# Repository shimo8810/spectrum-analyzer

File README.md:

# Spectrum Analyzer

This is a stereo 7-band spectrum analyzer utilizing the MSGEQ7.

## Tools

### LED Matrix Generator

this tool is for generating data for LED matrix.

[LED Matrix Generator Web App](https://shimo8810.github.io/spectrum-analyzer/)

## License

- Software: [MIT License](https://choosealicense.com/licenses/mit/)
- Hardware: [CERN Open Hardware License version 2.0](https://choosealicense.com/licenses/cern-ohl-p-2.0/)

## Acknowledgments

- [Equalizer icons created by Ehtisham Abid - Flaticon](https://www.flaticon.com/free-icons/equalizer)

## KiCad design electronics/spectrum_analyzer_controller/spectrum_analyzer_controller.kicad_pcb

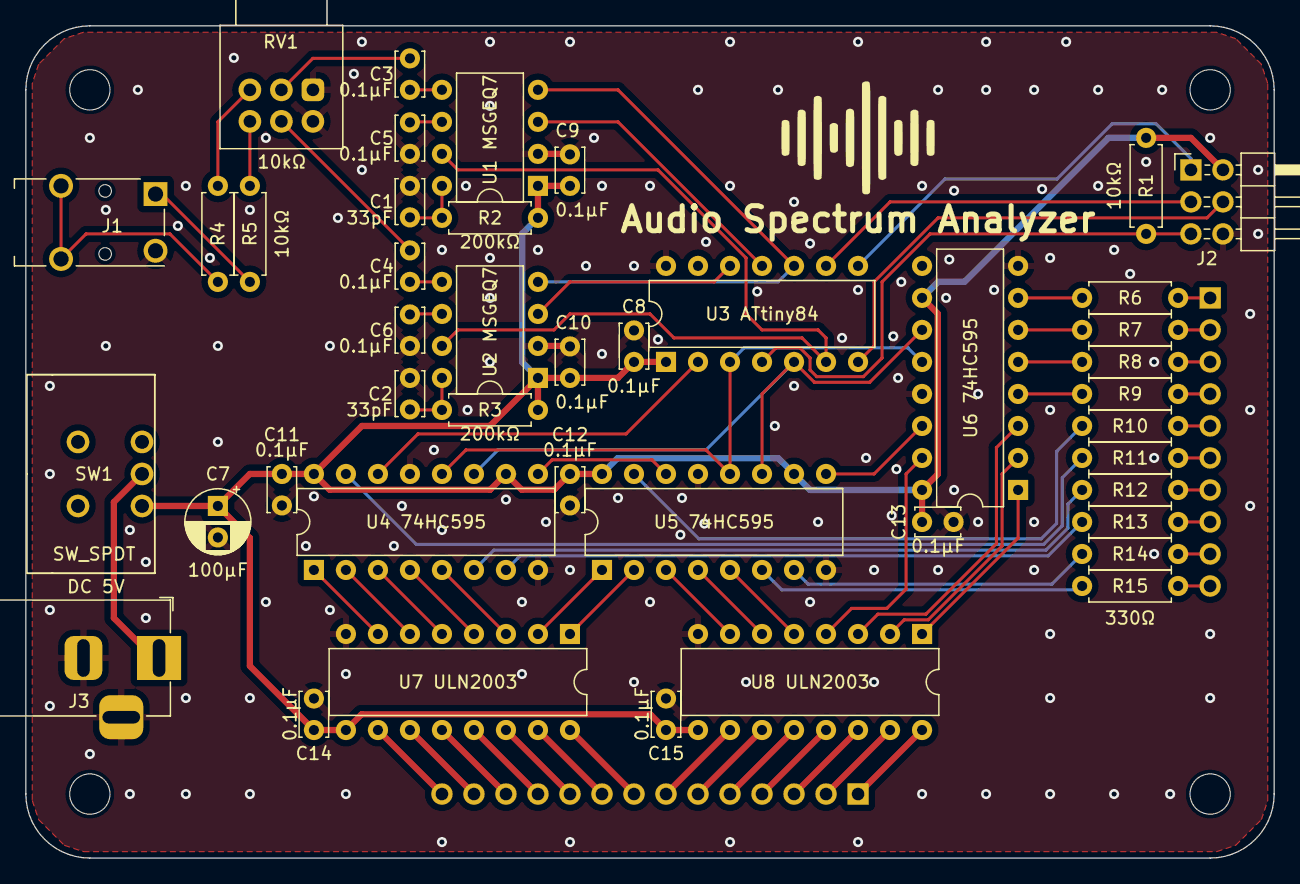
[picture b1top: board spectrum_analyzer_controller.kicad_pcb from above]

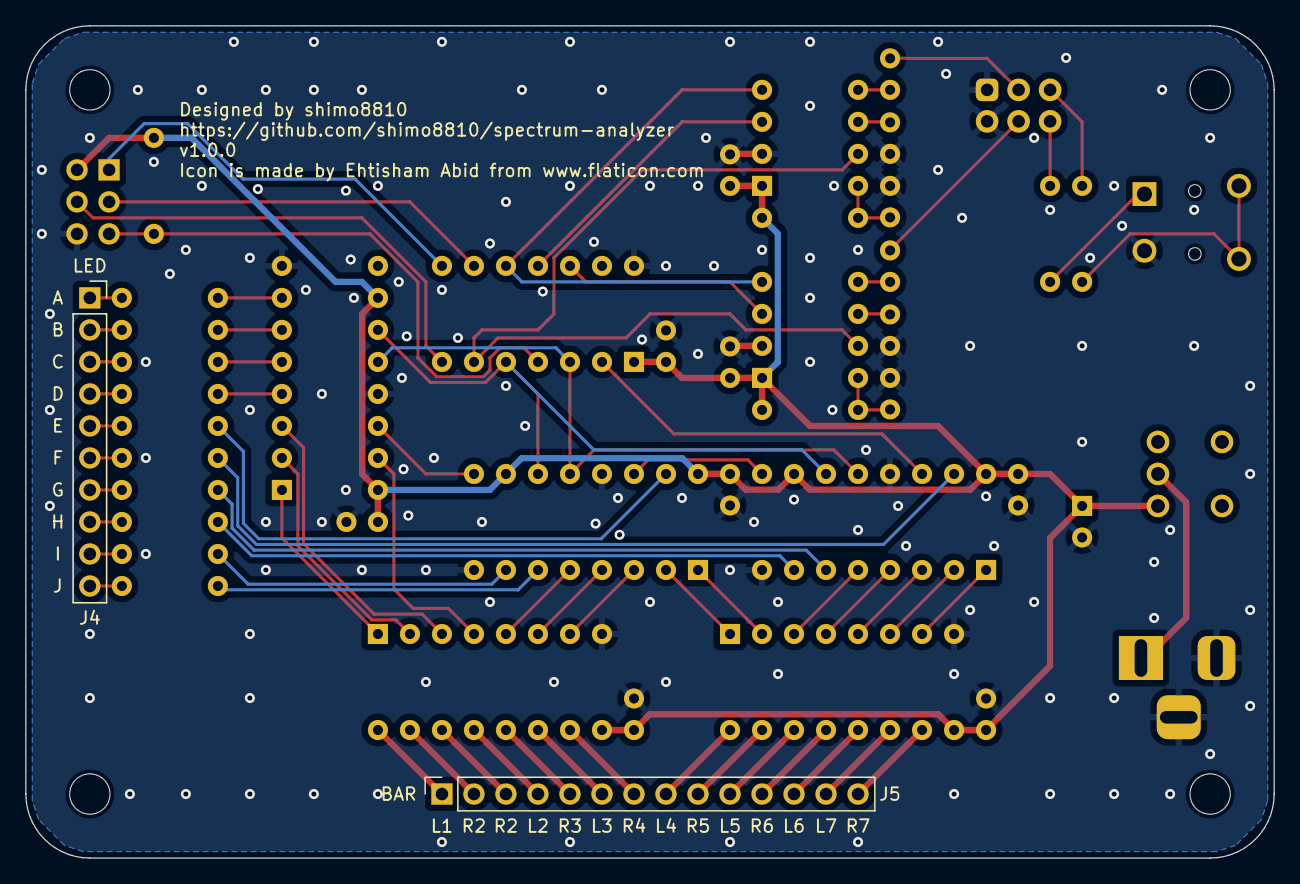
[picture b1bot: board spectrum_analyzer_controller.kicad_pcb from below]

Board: 2 copper layers, 99.1 x 66.0 mm, 50 parts (2 on the bottom side), 76 nets.

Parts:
C1, C2: 33p; C_Disc_D3.4mm_W2.1mm_P2.50mm
C3, C4, C5, C6, C8, C9, C10, C11, C12, C13, C14, C15: 0.1u; C_Disc_D3.4mm_W2.1mm_P2.50mm
C7: 100u; CP_Radial_D5.0mm_P2.50mm
G1: LOGO; equalizer_icon
J1: AudioJack3; Jack_3.5mm_Switronic_ST-005-G_horizontal
J2: Conn_02x03_Odd_Even; PinHeader_2x03_P2.54mm_Horizontal
J3: Barrel_Jack_Switch; BarrelJack_Horizontal
J4: Conn_01x10_Socket; PinSocket_1x10_P2.54mm_Vertical
J5: Conn_01x14_Socket; PinSocket_1x14_P2.54mm_Vertical
R1, R4, R5: 10k; SP_R_Axial_DIN0207_L6.3mm_D2.5mm_P7.62mm_Horizontal
R2, R3: 200k; SP_R_Axial_DIN0207_L6.3mm_D2.5mm_P7.62mm_Horizontal
R6, R7, R8, R9, R10, R11, R12, R13, R14, R15: 330; SP_R_Axial_DIN0207_L6.3mm_D2.5mm_P7.62mm_Horizontal
REF1, REF2, REF3, REF4: MountingHole_3.2mm_M3
RV1: 10k; Potentiometer_Alps_RK097_Dual_Horizontal
SW1: SW_SPDT; 4MS1R202M6QES
U1 MSGEQ7, U2 MSGEQ7: MSGEQ7; DIP-8_W7.62mm
U3 ATtiny84: ATtiny84-20P; DIP-14_W7.62mm
U4 74HC595, U5 74HC595, U6 74HC595: 74HC595; DIP-16_W7.62mm
U7 ULN2003, U8 ULN2003: ULN2003; DIP-16_W7.62mm

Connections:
+5V: C7.1, C8.1, C9.1, C10.1, C11.1, C12.1, C13.1, C14.1, C15.1, J2.2, R1.1, R2.1, R3.1, SW1.1 (A), U1 MSGEQ7.1 (VDD), U2 MSGEQ7.1 (VDD), U3 ATtiny84.1 (VCC), U4 74HC595.10 (~SRCLR), U4 74HC595.16 (VCC), U5 74HC595.10 (~SRCLR), U5 74HC595.16 (VCC), U6 74HC595.10 (~SRCLR), U6 74HC595.16 (VCC), U7 ULN2003.9 (COM), U8 ULN2003.9 (COM)
/GEQ_RESET: U1 MSGEQ7.7 (RESET), U2 MSGEQ7.7 (RESET), U3 ATtiny84.6 (PA7)
/ICSP_CLOCK: J2.3, U3 ATtiny84.9 (PA4)
/ICSP_MISO: J2.1, U3 ATtiny84.8 (PA5)
/ICSP_MOSI: J2.4, U3 ATtiny84.7 (PA6)
/LED_A: R6.1, U6 74HC595.7 (QH)
/LED_B: R7.1, U6 74HC595.6 (QG)
/LED_C: R8.1, U6 74HC595.5 (QF)
/LED_CLOCK: U3 ATtiny84.5 (PB2), U4 74HC595.11 (SRCLK), U5 74HC595.11 (SRCLK), U6 74HC595.11 (SRCLK)
/LED_D: R9.1, U6 74HC595.4 (QE)
/LED_DATA: U3 ATtiny84.2 (XTAL1/PB0), U4 74HC595.14 (SER)
/LED_E: R10.1, U5 74HC595.15 (QA)
/LED_F: R11.1, U4 74HC595.15 (QA)
/LED_G: R12.1, U4 74HC595.6 (QG)
/LED_H: R13.1, U4 74HC595.7 (QH)
/LED_I: R14.1, U5 74HC595.7 (QH)
/LED_J: R15.1, U5 74HC595.6 (QG)
/LED_LATCH: U3 ATtiny84.3 (XTAL2/PB1), U4 74HC595.12 (RCLK), U5 74HC595.12 (RCLK), U6 74HC595.12 (RCLK)
/LEFT_1: J5.1, U8 ULN2003.16 (O1)
/LEFT_2: J5.4, U8 ULN2003.13 (O4)
/LEFT_3: J5.6, U8 ULN2003.11 (O6)
/LEFT_4: J5.8, U7 ULN2003.16 (O1)
/LEFT_5: J5.10, U7 ULN2003.14 (O3)
/LEFT_6: J5.12, U7 ULN2003.12 (O5)
/LEFT_7: J5.13, U7 ULN2003.11 (O6)
/LEFT_IN: C3.1, U1 MSGEQ7.5 (IN)
/LEFT_OUT: U1 MSGEQ7.3 (OUT), U3 ATtiny84.11 (PA2)
/RESET: J2.5, R1.2, U3 ATtiny84.4 (~RESET/PB3)
/RIGHT_1: J5.2, U8 ULN2003.15 (O2)
/RIGHT_2: J5.3, U8 ULN2003.14 (O3)
/RIGHT_3: J5.5, U8 ULN2003.12 (O5)
/RIGHT_4: J5.7, U8 ULN2003.10 (O7)
/RIGHT_5: J5.9, U7 ULN2003.15 (O2)
/RIGHT_6: J5.11, U7 ULN2003.13 (O4)
/RIGHT_7: J5.14, U7 ULN2003.10 (O7)
/RIGHT_IN: C4.1, U2 MSGEQ7.5 (IN)
/RIGHT_OUT: U2 MSGEQ7.3 (OUT), U3 ATtiny84.12 (PA1)
/STROBE: U1 MSGEQ7.4 (STROBE), U2 MSGEQ7.4 (STROBE), U3 ATtiny84.10 (PA3)
GND: C1.2, C2.2, C5.2, C6.2, C7.2, C8.2, C9.2, C10.2, C11.2, C12.2, C13.2, C14.2, C15.2, J1.S, J2.6, J3.2, J3.3, RV1.1, RV1.4, U1 MSGEQ7.2 (VSS), U2 MSGEQ7.2 (VSS), U3 ATtiny84.14 (GND), U4 74HC595.8 (GND), U4 74HC595.13 (~OE), U5 74HC595.8 (GND), U5 74HC595.13 (~OE), U6 74HC595.8 (GND), U6 74HC595.13 (~OE), U7 ULN2003.8 (GND), U8 ULN2003.8 (GND)
unnamed: C3.2, RV1.2
unnamed: C4.2, RV1.5
unnamed: J1.R, R5.1
unnamed: J1.T, R4.2
unnamed: J4.1, R6.2
unnamed: J4.2, R7.2
unnamed: J4.3, R8.2
unnamed: J4.4, R9.2
unnamed: J4.5, R10.2
unnamed: J4.6, R11.2
unnamed: J4.7, R12.2
unnamed: J4.8, R13.2
unnamed: J4.9, R14.2
unnamed: J4.10, R15.2
unnamed: R4.1, RV1.3
unnamed: R5.2, RV1.6
unnamed: C1.1, R2.2, U1 MSGEQ7.8 (CKIN)
unnamed: C5.1, U1 MSGEQ7.6 (GND)
unnamed: C2.1, R3.2, U2 MSGEQ7.8 (CKIN)
unnamed: C6.1, U2 MSGEQ7.6 (GND)
unnamed: U4 74HC595.1 (QB), U7 ULN2003.7 (I7)
unnamed: U4 74HC595.2 (QC), U7 ULN2003.6 (I6)
unnamed: U4 74HC595.3 (QD), U7 ULN2003.5 (I5)
unnamed: U4 74HC595.4 (QE), U7 ULN2003.4 (I4)
unnamed: U4 74HC595.5 (QF), U7 ULN2003.3 (I3)
unnamed: U4 74HC595.9 (QH'), U5 74HC595.14 (SER)
unnamed: U5 74HC595.1 (QB), U7 ULN2003.2 (I2)
unnamed: U5 74HC595.2 (QC), U7 ULN2003.1 (I1)
unnamed: U5 74HC595.3 (QD), U8 ULN2003.7 (I7)
unnamed: U5 74HC595.4 (QE), U8 ULN2003.6 (I6)
unnamed: U5 74HC595.5 (QF), U8 ULN2003.5 (I5)
unnamed: U5 74HC595.9 (QH'), U6 74HC595.14 (SER)
unnamed: U6 74HC595.15 (QA), U8 ULN2003.4 (I4)
unnamed: U6 74HC595.1 (QB), U8 ULN2003.1 (I1)
unnamed: U6 74HC595.2 (QC), U8 ULN2003.2 (I2)
unnamed: U6 74HC595.3 (QD), U8 ULN2003.3 (I3)
VDC: J3.1, SW1.2 (B)

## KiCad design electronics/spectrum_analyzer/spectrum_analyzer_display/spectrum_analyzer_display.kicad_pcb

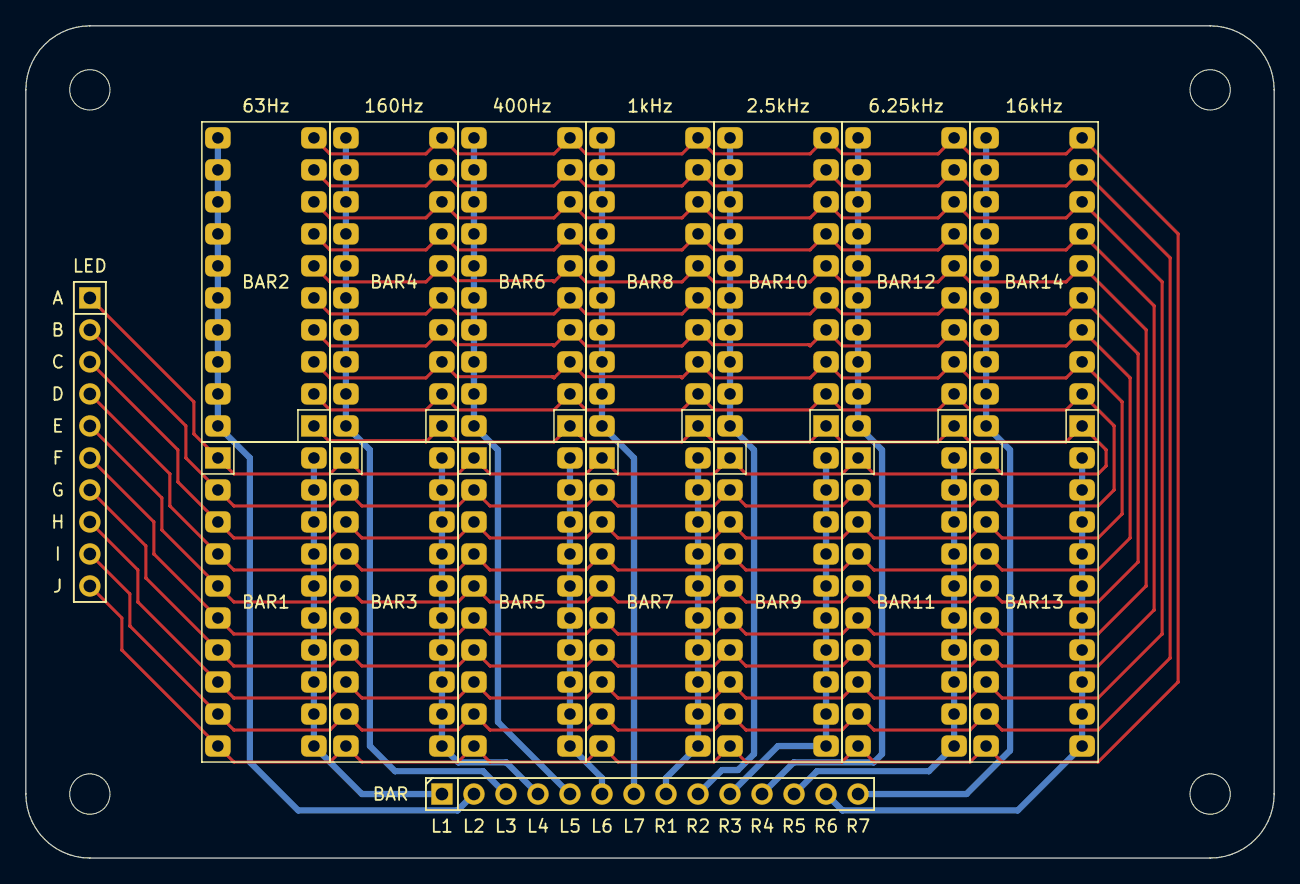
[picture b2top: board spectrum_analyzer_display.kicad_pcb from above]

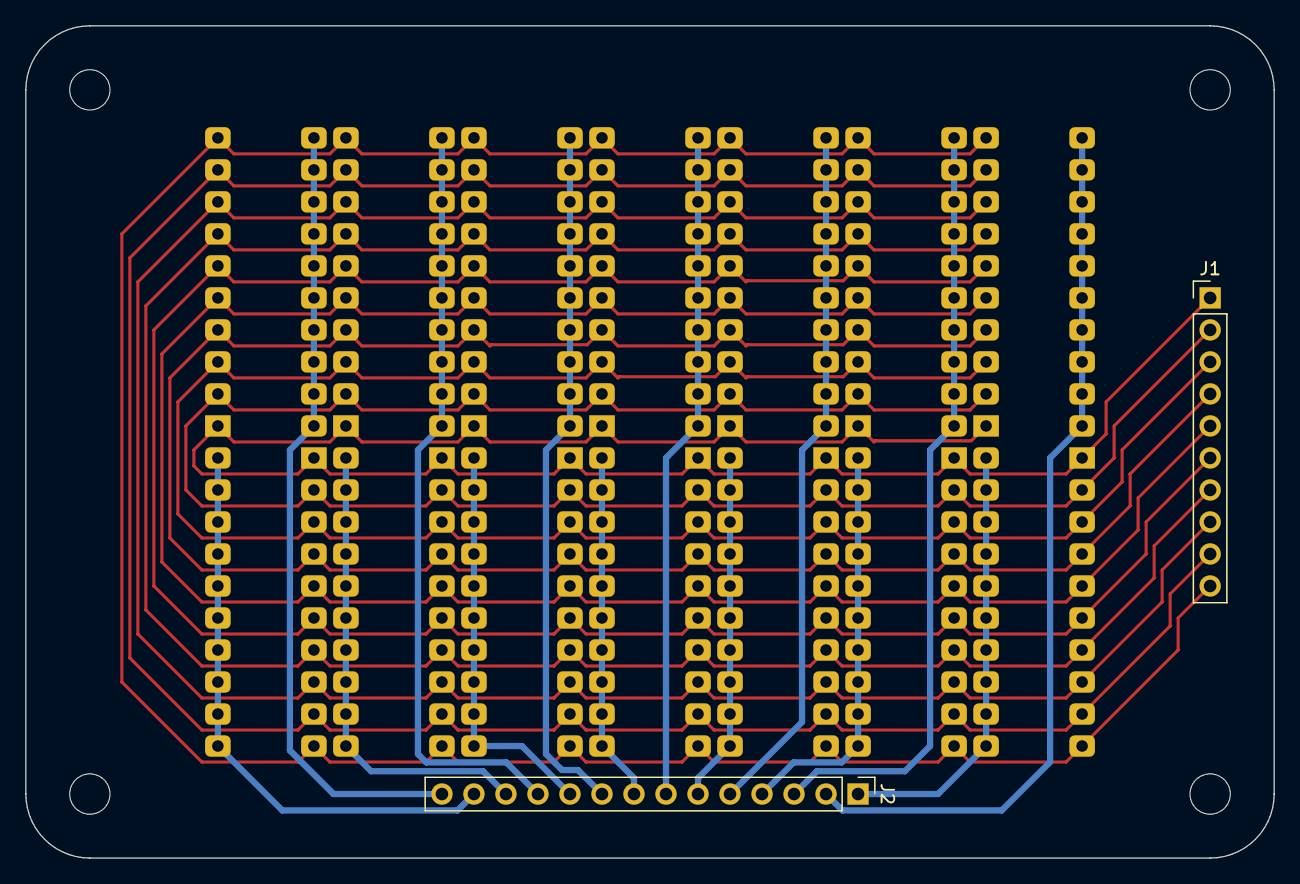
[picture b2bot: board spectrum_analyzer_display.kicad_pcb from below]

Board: 2 copper layers, 99.1 x 66.0 mm, 20 parts (2 on the bottom side), 24 nets.

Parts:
BAR1, BAR2, BAR3, BAR4, BAR5, BAR6, BAR7, BAR8, BAR9, BAR10, BAR11, BAR12, BAR13, BAR14: HDSP-4832_2; SP_HDSP-4832
J1: Conn_01x10_Pin; PinHeader_1x10_P2.54mm_Vertical
J2: Conn_01x14_Pin; PinHeader_1x14_P2.54mm_Vertical
REF1, REF2, REF3, REF4: MountingHole_3.2mm_M3

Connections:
/A: BAR1.1 (A), BAR2.1 (A), BAR3.1 (A), BAR4.1 (A), BAR5.1 (A), BAR6.1 (A), BAR7.1 (A), BAR8.1 (A), BAR9.1 (A), BAR10.1 (A), BAR11.1 (A), BAR12.1 (A), BAR13.1 (A), BAR14.1 (A), J1.1
/B: BAR1.2 (A), BAR2.2 (A), BAR3.2 (A), BAR4.2 (A), BAR5.2 (A), BAR6.2 (A), BAR7.2 (A), BAR8.2 (A), BAR9.2 (A), BAR10.2 (A), BAR11.2 (A), BAR12.2 (A), BAR13.2 (A), BAR14.2 (A), J1.2
/C: BAR1.3 (A), BAR2.3 (A), BAR3.3 (A), BAR4.3 (A), BAR5.3 (A), BAR6.3 (A), BAR7.3 (A), BAR8.3 (A), BAR9.3 (A), BAR10.3 (A), BAR11.3 (A), BAR12.3 (A), BAR13.3 (A), BAR14.3 (A), J1.3
/D: BAR1.4 (A), BAR2.4 (A), BAR3.4 (A), BAR4.4 (A), BAR5.4 (A), BAR6.4 (A), BAR7.4 (A), BAR8.4 (A), BAR9.4 (A), BAR10.4 (A), BAR11.4 (A), BAR12.4 (A), BAR13.4 (A), BAR14.4 (A), J1.4
/E: BAR1.5 (A), BAR2.5 (A), BAR3.5 (A), BAR4.5 (A), BAR5.5 (A), BAR6.5 (A), BAR7.5 (A), BAR8.5 (A), BAR9.5 (A), BAR10.5 (A), BAR11.5 (A), BAR12.5 (A), BAR13.5 (A), BAR14.5 (A), J1.5
/F: BAR1.6 (A), BAR2.6 (A), BAR3.6 (A), BAR4.6 (A), BAR5.6 (A), BAR6.6 (A), BAR7.6 (A), BAR8.6 (A), BAR9.6 (A), BAR10.6 (A), BAR11.6 (A), BAR12.6 (A), BAR13.6 (A), BAR14.6 (A), J1.6
/G: BAR1.7 (A), BAR2.7 (A), BAR3.7 (A), BAR4.7 (A), BAR5.7 (A), BAR6.7 (A), BAR7.7 (A), BAR8.7 (A), BAR9.7 (A), BAR10.7 (A), BAR11.7 (A), BAR12.7 (A), BAR13.7 (A), BAR14.7 (A), J1.7
/H: BAR1.8 (A), BAR2.8 (A), BAR3.8 (A), BAR4.8 (A), BAR5.8 (A), BAR6.8 (A), BAR7.8 (A), BAR8.8 (A), BAR9.8 (A), BAR10.8 (A), BAR11.8 (A), BAR12.8 (A), BAR13.8 (A), BAR14.8 (A), J1.8
/I: BAR1.9 (A), BAR2.9 (A), BAR3.9 (A), BAR4.9 (A), BAR5.9 (A), BAR6.9 (A), BAR7.9 (A), BAR8.9 (A), BAR9.9 (A), BAR10.9 (A), BAR11.9 (A), BAR12.9 (A), BAR13.9 (A), BAR14.9 (A), J1.9
/J: BAR1.10 (A), BAR2.10 (A), BAR3.10 (A), BAR4.10 (A), BAR5.10 (A), BAR6.10 (A), BAR7.10 (A), BAR8.10 (A), BAR9.10 (A), BAR10.10 (A), BAR11.10 (A), BAR12.10 (A), BAR13.10 (A), BAR14.10 (A), J1.10
/LEFT_1: BAR1.11 (K), BAR1.12 (K), BAR1.13 (K), BAR1.14 (K), BAR1.15 (K), BAR1.16 (K), BAR1.17 (K), BAR1.18 (K), BAR1.19 (K), BAR1.20 (K), J2.1
/LEFT_2: BAR3.11 (K), BAR3.12 (K), BAR3.13 (K), BAR3.14 (K), BAR3.15 (K), BAR3.16 (K), BAR3.17 (K), BAR3.18 (K), BAR3.19 (K), BAR3.20 (K), J2.4
/LEFT_3: BAR5.11 (K), BAR5.12 (K), BAR5.13 (K), BAR5.14 (K), BAR5.15 (K), BAR5.16 (K), BAR5.17 (K), BAR5.18 (K), BAR5.19 (K), BAR5.20 (K), J2.6
/LEFT_4: BAR7.11 (K), BAR7.12 (K), BAR7.13 (K), BAR7.14 (K), BAR7.15 (K), BAR7.16 (K), BAR7.17 (K), BAR7.18 (K), BAR7.19 (K), BAR7.20 (K), J2.8
/LEFT_5: BAR9.11 (K), BAR9.12 (K), BAR9.13 (K), BAR9.14 (K), BAR9.15 (K), BAR9.16 (K), BAR9.17 (K), BAR9.18 (K), BAR9.19 (K), BAR9.20 (K), J2.10
/LEFT_6: BAR11.11 (K), BAR11.12 (K), BAR11.13 (K), BAR11.14 (K), BAR11.15 (K), BAR11.16 (K), BAR11.17 (K), BAR11.18 (K), BAR11.19 (K), BAR11.20 (K), J2.12
/LEFT_7: BAR13.11 (K), BAR13.12 (K), BAR13.13 (K), BAR13.14 (K), BAR13.15 (K), BAR13.16 (K), BAR13.17 (K), BAR13.18 (K), BAR13.19 (K), BAR13.20 (K), J2.13
/RIGHT_1: BAR2.11 (K), BAR2.12 (K), BAR2.13 (K), BAR2.14 (K), BAR2.15 (K), BAR2.16 (K), BAR2.17 (K), BAR2.18 (K), BAR2.19 (K), BAR2.20 (K), J2.2
/RIGHT_2: BAR4.11 (K), BAR4.12 (K), BAR4.13 (K), BAR4.14 (K), BAR4.15 (K), BAR4.16 (K), BAR4.17 (K), BAR4.18 (K), BAR4.19 (K), BAR4.20 (K), J2.3
/RIGHT_3: BAR6.11 (K), BAR6.12 (K), BAR6.13 (K), BAR6.14 (K), BAR6.15 (K), BAR6.16 (K), BAR6.17 (K), BAR6.18 (K), BAR6.19 (K), BAR6.20 (K), J2.5
/RIGHT_4: BAR8.11 (K), BAR8.12 (K), BAR8.13 (K), BAR8.14 (K), BAR8.15 (K), BAR8.16 (K), BAR8.17 (K), BAR8.18 (K), BAR8.19 (K), BAR8.20 (K), J2.7
/RIGHT_5: BAR10.11 (K), BAR10.12 (K), BAR10.13 (K), BAR10.14 (K), BAR10.15 (K), BAR10.16 (K), BAR10.17 (K), BAR10.18 (K), BAR10.19 (K), BAR10.20 (K), J2.9
/RIGHT_6: BAR12.11 (K), BAR12.12 (K), BAR12.13 (K), BAR12.14 (K), BAR12.15 (K), BAR12.16 (K), BAR12.17 (K), BAR12.18 (K), BAR12.19 (K), BAR12.20 (K), J2.11
/RIGHT_7: BAR14.11 (K), BAR14.12 (K), BAR14.13 (K), BAR14.14 (K), BAR14.15 (K), BAR14.16 (K), BAR14.17 (K), BAR14.18 (K), BAR14.19 (K), BAR14.20 (K), J2.14

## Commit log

2023-07-25 doc: change name
2023-07-25 chore: ignore kicad files
2023-08-03 feat: add shematics
2023-08-03 Create hardware-LICENSE
2023-08-03 feat: change wire width
2023-08-06 chore: add lisence and acknowledgments
2023-08-06 feat: add 3d models
2023-08-06 feat: update shematics
2023-08-06 chore: add design image
2023-08-06 chore: remove zip files
2023-08-06 chore: add stl files
2023-08-17 feat: change pcb layout and enclosure design
2023-08-17 chore: remove files
2023-08-17 chore: remove backup file
2023-08-17 chore: ignore release dir
2023-08-17 chore: remove release dir
2023-08-17 chore: change license files
2023-08-17 chore: move license files
2023-08-30 fix: update incorrect wiring of the circuit
2023-09-03 chore: update data
2023-09-03 chore: ignore /target directory
2023-09-03 build: add build info
2023-09-03 build: add attiny84 spec file
2023-09-03 chore: add dep package
2023-09-03 build: change toolchain version
2023-09-03 chore: add script to upload elf file
2023-09-03 feat: add sample code
2023-09-03 refactor: sort libs
2023-09-03 refactor: separete delay and led matrix from main.rs
2023-09-03 feat: add show led by matrix
2023-09-03 feat(wip): test led matrix
2023-09-09 feat: remove rust firmware code
2023-09-09 chore: exclude arduino setting and build files from git
2023-09-09 chore: exclude vscode settings from git
2023-09-09 feat: add firmware.ino
2023-09-10 chore: remove lck files
2023-09-10 feat: add led-matrix-generator tool
2023-09-10 style: fix style
2023-09-10 chore: change github pages config
2023-09-10 feat: add pwd
2023-09-10 chore: change cache dir
2023-09-10 chore: change upload path
2023-09-10 docs: add images for readme
2023-09-10 docs: add image of webui
